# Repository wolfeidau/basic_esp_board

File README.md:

# basic_esp_board

This is a simple ESP8266 based board i am working on designing using KiCad.

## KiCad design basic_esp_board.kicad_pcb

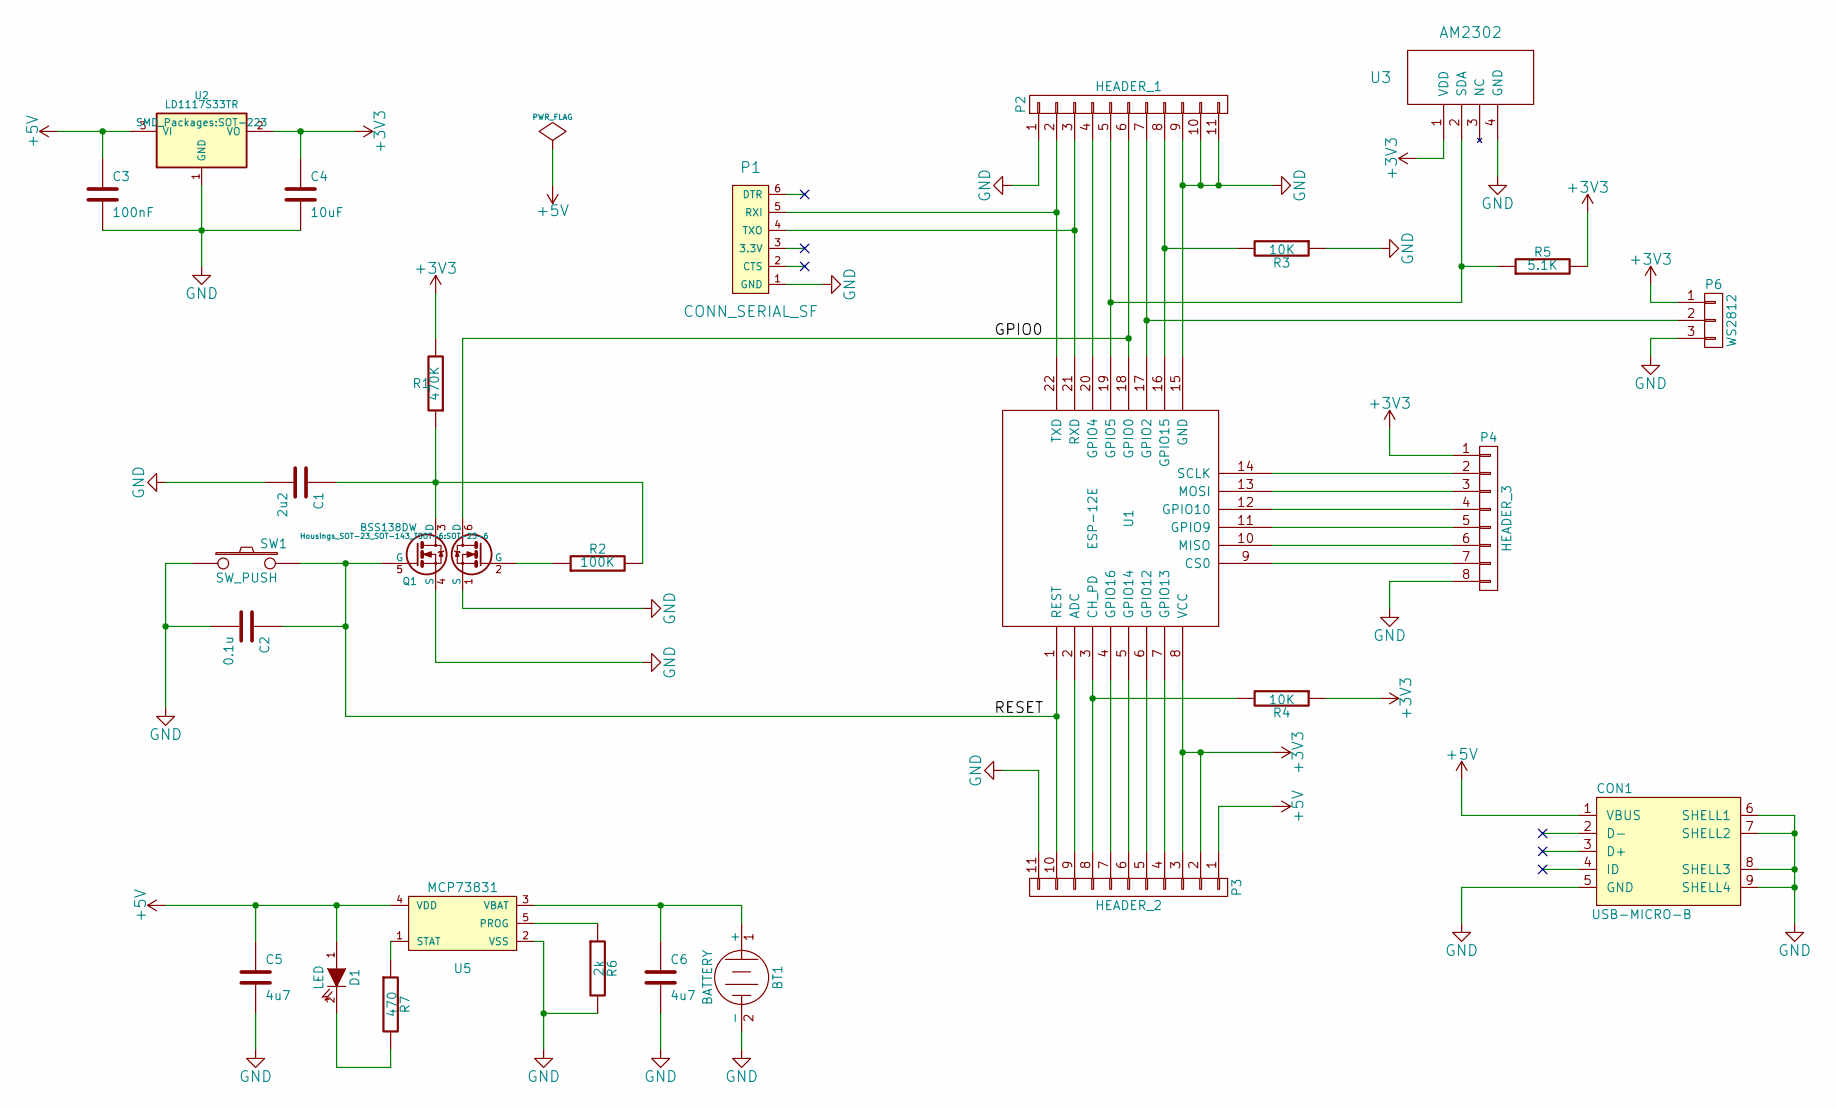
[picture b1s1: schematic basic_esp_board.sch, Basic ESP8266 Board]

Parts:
BT1: BATTERY; Pin_Header_Straight_1x02
C1: 2u2; C_0805
C2: 0.1u; C_0805
C3: 100nF; C_0805
C4: 10uF; C_0805
C5, C6: 4u7; C_0805
CON1: USB-MICRO-B; USB_Micro-B
D1: LED; LED-0805
P1: CONN_SERIAL_SF; Pin_Header_Straight_1x06
P2: HEADER_1; Socket_Strip_Straight_1x11
P3: HEADER_2; Socket_Strip_Straight_1x11
P4: HEADER_3; Socket_Strip_Straight_1x08
P6: WS2812; Pin_Header_Straight_1x03
Q1: BSS138DW; SOT-23-6
R1: 470K; R_0805
R2: 100K; R_0805
R3, R4: 10K; R_0805
R5: 5.1K; R_0805
R6: 2k; R_0805
R7: 470; R_0805
SW1: SW_PUSH; 1107G
U1: ESP-12E
U2: LD1117S33TR; SOT-223
U3: AM2302; Pin_Header_Straight_1x04
U5: MCP73831; SOT-23-5

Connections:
+3V3: C4.1, P3.2, P3.3, P4.1, P6.1, R1.2, R4.1, R5.2, U1.8 (VCC), U2.2 (VO), U3.1 (VDD)
+5V: C3.1, C5.1, CON1.1 (VBUS), D1.1 (A), P3.1, U2.3 (VI), U5.4 (VDD)
/GPIO0: P2.6, Q1.6 (D), U1.18 (GPIO0)
/RESET: C2.1, P3.10, Q1.5 (G), SW1.2, U1.1 (REST)
GND: BT1.2 (-), C1.2, C2.2, C3.2, C4.2, C5.2, C6.2, CON1.5 (GND), CON1.6 (SHELL1), CON1.7 (SHELL2), CON1.8 (SHELL3), CON1.9 (SHELL4), P1.1 (GND), P2.1, P2.9, P2.10, P2.11, P3.11, P4.8, P6.3, Q1.1 (S), Q1.4 (S), R3.1, R6.2, SW1.1, U1.15 (GND), U2.1 (GND), U3.4 (GND), U5.2 (VSS)
unnamed: BT1.1 (+), C6.1, U5.3 (VBAT)
unnamed: C1.1, Q1.3 (D), R1.1, R2.2
unnamed: D1.2 (K), R7.2
unnamed: P1.4 (TXO), P2.3, U1.21 (RXD)
unnamed: P1.5 (RXI), P2.2, U1.22 (TXD)
unnamed: P2.4, U1.20 (GPIO4)
unnamed: P2.5, R5.1, U1.19 (GPIO5), U3.2 (SDA)
unnamed: P2.7, P6.2, U1.17 (GPIO2)
unnamed: P2.8, R3.2, U1.16 (GPIO15)
unnamed: P3.4, U1.7 (GPIO13)
unnamed: P3.5, U1.6 (GPIO12)
unnamed: P3.6, U1.5 (GPIO14)
unnamed: P3.7, U1.4 (GPIO16)
unnamed: P3.8, R4.2, U1.3 (CH_PD)
unnamed: P3.9, U1.2 (ADC)
unnamed: P4.2, U1.14 (SCLK)
unnamed: P4.3, U1.13 (MOSI)
unnamed: P4.4, U1.12 (GPIO10)
unnamed: P4.5, U1.11 (GPIO9)
unnamed: P4.6, U1.10 (MISO)
unnamed: P4.7, U1.9 (CS0)
unnamed: Q1.2 (G), R2.1
unnamed: R6.1, U5.5 (PROG)
unnamed: R7.1, U5.1 (STAT)

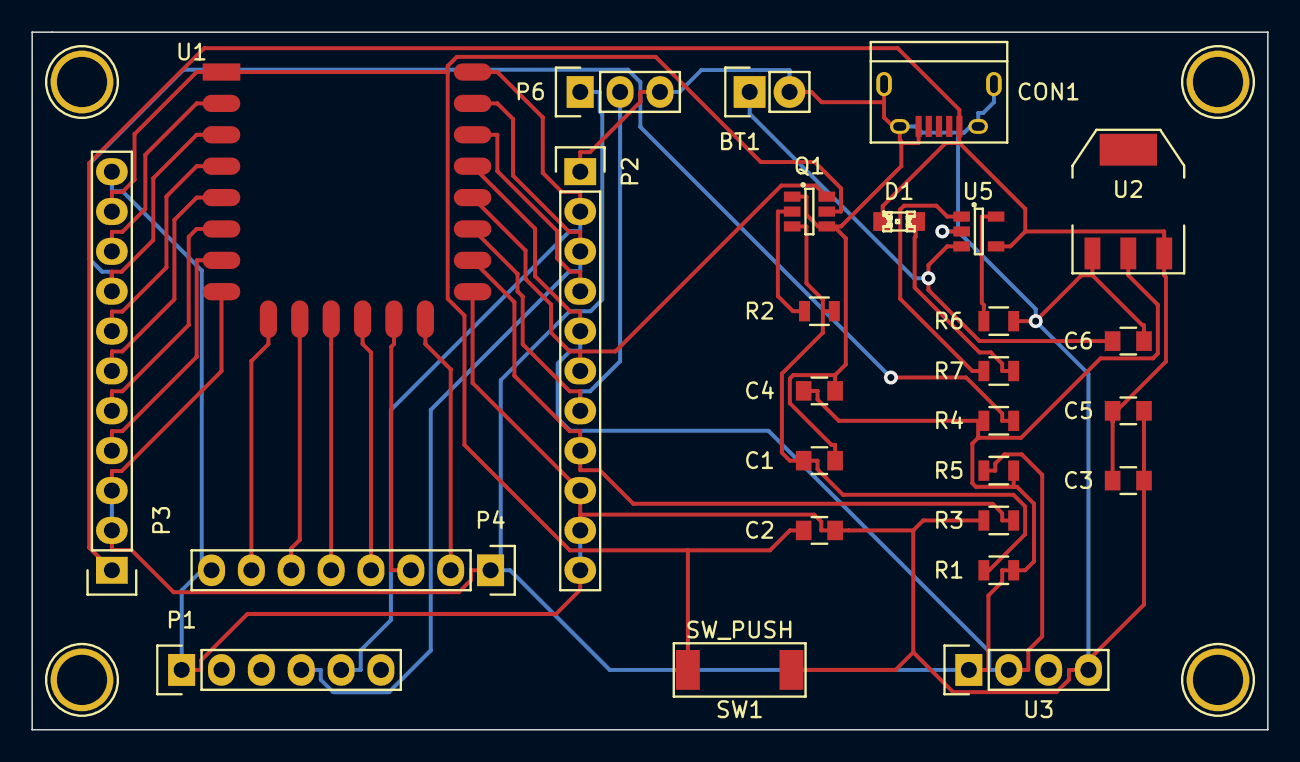
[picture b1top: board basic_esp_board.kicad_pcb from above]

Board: 2 copper layers, 78.7 x 44.4 mm, 31 parts (0 on the bottom side), 29 nets.

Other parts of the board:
Z1, Z2, Z3, Z4: 1pin

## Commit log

2015-07-08 Initial import.
2015-07-08 Added Lithium Battery Charger with Load Sharing.
2015-07-08 Added PDF plot.
2015-07-08 Fixed some of the circuits and merged transistors.
2015-07-13 Initial cut sent for first run.
2015-08-22 Circuit layout.
2015-08-22 Rejigged the board based on feedback from @projectgus
2015-08-25 Add pullup on GPIO2, change LDO type again, add FT footprint module and Hirose ZX62 USB connector
2015-08-25 Reroute board for new schematic, add ground plane
